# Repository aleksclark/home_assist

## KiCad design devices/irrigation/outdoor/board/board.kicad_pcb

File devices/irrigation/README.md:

# Irrigation Control

> **Status:** Planned

Two ESP32-based nodes for moisture sensing and automated irrigation.

## Nodes

### Indoor (`indoor/`)

- **Purpose:** Houseplant watering
- **Outputs:** 4 peristaltic pumps (one per plant/zone)
- **Sensors:** Capacitive soil moisture sensors
- **Board:** _TBD_

### Outdoor (`outdoor/`)

- **Purpose:** Garden drip irrigation
- **Outputs:** 4 solenoid valves controlling drip lines
- **Sensors:** Capacitive soil moisture sensors
- **Board:** _TBD_
- **Power:** Likely 24VAC solenoids with relay board

## Planned Features

- Per-zone moisture thresholds with hysteresis
- Manual override via Home Assistant
- Watering schedule fallback if HA is unreachable
- Moisture history logging

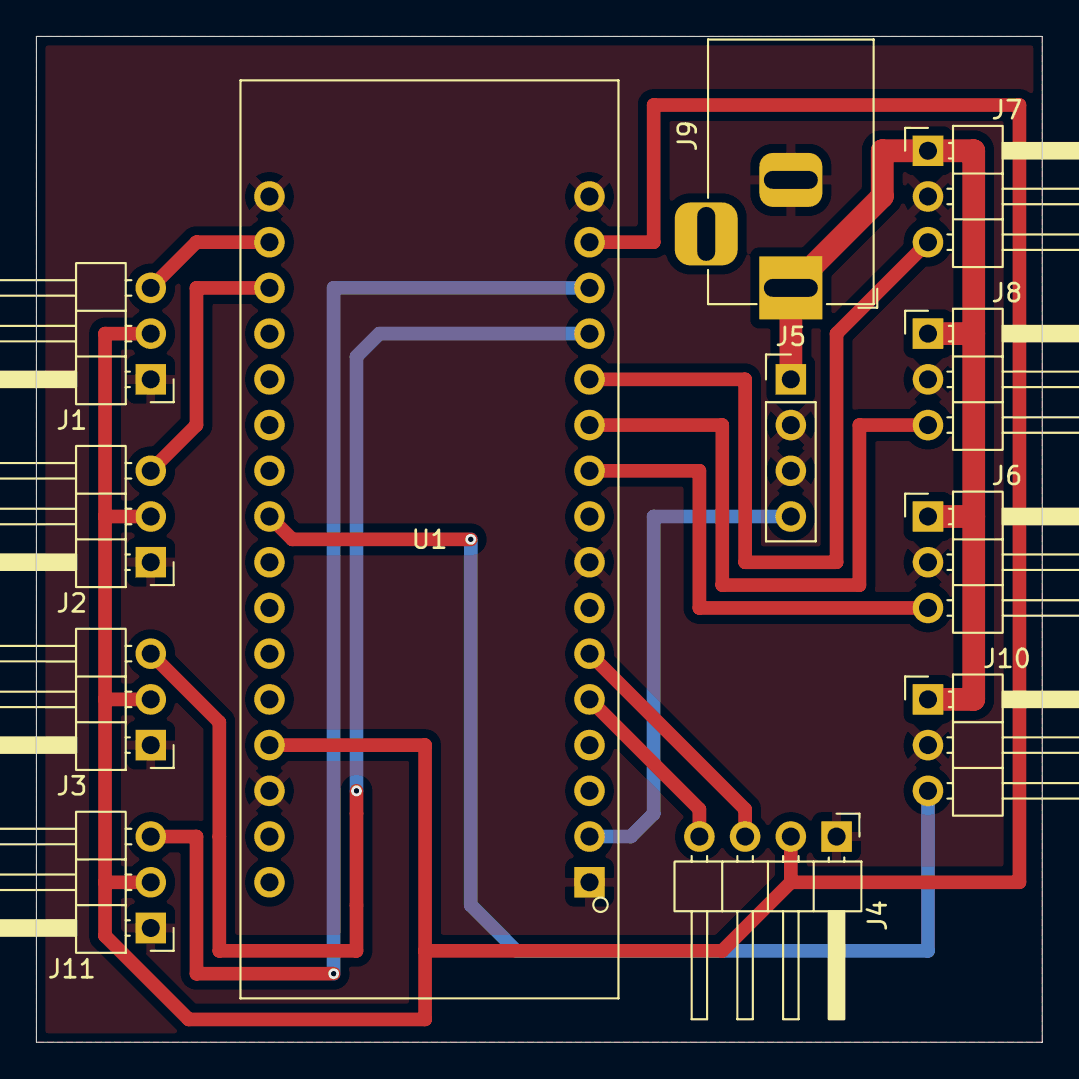
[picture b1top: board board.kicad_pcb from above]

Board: 2 copper layers, 55.9 x 55.9 mm, 12 parts (0 on the bottom side), 14 nets.

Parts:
J1, J2, J3, J11: Cap Sensor; PinHeader_1x03_P2.54mm_Horizontal
J4: GME12864; PinHeader_1x04_P2.54mm_Horizontal
J5: BUCK Conv; PinHeader_1x04_P2.54mm_Vertical
J6, J7, J8, J10: Relay Board; PinHeader_1x03_P2.54mm_Horizontal
J9: Barrel_Jack_MountingPin; BarrelJack_Horizontal
U1: CORE-ESP32-C3

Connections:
+3.3V: J1.2, J2.2, J3.2, J4.2, J11.2, U1.15 (+3V3), U1.20 (+3V3)
+5V: J5.4, U1.2 (VBUS)
+12V: J5.1, J6.1, J7.1, J8.1, J9.1, J10.1
GND: J1.1, J2.1, J3.1, J4.1, J5.2, J5.3, J6.2, J7.2, J8.2, J9.2, J10.2, J11.1, U1.1 (GND), U1.8 (GND), U1.16 (GND), U1.19 (GND), U1.32 (GND)
unnamed: J1.3, U1.31 (GPIO00/U1TXD)
unnamed: J2.3, U1.30 (GPIO01/U1RXD)
unnamed: J3.3, U1.13 (GPIO3)
unnamed: J4.3, U1.6 (GPIO5/ADC2/SCL)
unnamed: J4.4, U1.5 (GPIO4/ADC1/SDA)
unnamed: J6.3, U1.10 (GPIO7)
unnamed: J7.3, U1.12 (GPIO10)
unnamed: J8.3, U1.11 (GPIO6)
unnamed: J10.3, U1.25 (U0RXD)
unnamed: J11.3, U1.14 (GPIO2)

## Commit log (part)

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2026-03-07 Reorganize repo from flat bt_track/ into structured project layout
    Split the monolithic bt_track directory into devices/, esphome/, tools/,
    and home-assistant/ to cleanly separate device types and accommodate
    current and future projects (status display, irrigation nodes).
    🐘 Generated with Crush
    Assisted-by: AWS Claude Opus 4.6 via Crush <crush@charm.land>
2026-03-07 Add status display ESP32 firmware and ecobee research docs
    Status display: Rust firmware for ESP32-2432S028 (CYD) that registers
    with Home Assistant as a mobile_app device via webhook API and renders
    live sensor data (kitchen/bedroom temps, Della mini split, Ecobee) with
    incremental redraws. Code split into ha.rs (HA communication) and ui.rs
    (rendering/layout).
    Ecobee: research documents for ECB701 heat pump wiring diagnosis.
2026-03-10 Update Della mini split docs: rename to room-based entities, add kitchen AC
    - Recommend OpenBeken over ESPHome approach
    - Document WiFi AP configuration flow for OpenBeken modules
    - Rename existing entity from climate.della_mini_split to climate.livingroom_ac
    - Add second climate entity config for kitchen unit (climate.kitchen_ac)
    🐾 Generated with Crush
    Assisted-by: AWS Claude Opus 4.6 via Crush <crush@charm.land>
2026-03-12 Add outdoor irrigation controller and Della ESPHome config
    Outdoor irrigation: ESP32-C3 ESPHome firmware with 4-zone soil moisture
    sensing (ADC), 4 relay-controlled solenoid valves, SSD1306 OLED display,
    and Home Assistant integration. Includes wiring diagram and KiCad board.
    Della mini-splits: add custom TCL climate component for ESPHome migration,
    config YAML, setup docs, and Amos bedroom AC to HA MQTT config.
    🐮 Generated with Crush
2026-03-23 Fix HVAC automations, add display touch/dimming, persist HA config
    HVAC: fix boundary comparisons (<= / >=), switch Della automations to
    direct MQTT publish to bypass duplicate-entity conflicts, silence buzzer
    before each mode change, set daytime cool max to 73F.
    Status display: fix flicker with background-colored text rendering, add
    XPT2046 touch input and LEDC PWM backlight (dim after 3min, off after
    5min, tap to wake at 100%), fix display_status() to show actual HVAC
2026-04-13 fleet/blockyard: fix ansible deploy, add playbooks
    - Fix host_vars resolution: symlink host_vars/group_vars into
    inventory/ dir so Ansible finds them when inventory is specified
    as inventory/hosts.yml in ansible.cfg
    - systemd unit: add TimeoutStopSec=10, KillMode=mixed, SendSIGKILL
    to prevent systemctl stop from hanging when blockyard is stuck in
    Raft retry loops
2026-04-15 fix(hvac): reconcile automations, add deadband, remove Ecobee refs
    - Reconcile reference automations with live: use direct mqtt.publish
    with F-to-C conversion for Della units (was using climate.set_temperature
    which sends Fahrenheit through the entity layer)
    - Add 1.5°F deadband/hysteresis to all Della automations to prevent
    rapid cycling when temp oscillates around setpoint boundaries
    - Fix input_helpers.yaml daytime_cool_f initial: 75 -> 73 to match live
2026-04-15 Fix daytime cooling threshold to 74°F, align all HVAC config files
    Daytime cool setpoint was 73°F in deployed config and 75°F in reference
    config — standardized to 74°F across all files. Also corrected daytime
    heat_min comments/zones from 68→65 to match actual input_number values.
    🐘 Generated with Crush
    Assisted-by: AWS Claude Opus 4.6 via Crush <crush@charm.land>
2026-04-17 feat(hvac): add input_select.hvac_schedule_period to HA config
    New helper for the schedule dispatcher automation.
    Added include line to configuration.yaml.
2026-04-18 tcl_climate: add HEAT_COOL dual-setpoint mode
    When set to heat_cool, the ESP autonomously switches between heat and
    cool modes based on current temperature vs low/high setpoints. Reports
    HEAT_COOL to HA with two-point sliders while internally toggling the
    single-setpoint TCL protocol.
    In the deadband (between low and high), if the unit is already heating
    or cooling it keeps going. If idle, picks direction based on which side
2026-04-22 Update migration plan: NAS becomes node-4
    Major revision to account for NAS being wiped and reinstalled as
    node-4 in the fleet. Key changes:
    - 7-phase migration order designed for minimal disruption
    - Services migrate to fleet BEFORE NAS is touched
    - NAS converts last, bringing 4x5.5TB + 32GB RAM + QSV to the cluster
    - Jellyfin/PhotoPrism temporarily lose HW transcoding during soak,
2026-04-24 Update migration plan: reflect hardware additions
    - node-1: added 2x 1.8TB drives + 2.5G NIC (bond0)
    - node-2: added 1x 1.8TB drive + 2.5G NIC (bond0)
    - node-3: added 2.5G NIC (bond0)
    - All nodes now have balance-alb bonds (1G+2.5G)
    - Cluster now ~26TB raw (~10TB avail), up from ~18.5TB
    - Post node-4 conversion: ~48TB raw (was ~38TB)
2026-04-24 Migrate omada-controller from NAS to Nomad/node-3
    - Stopped on NAS, synced volumes to MooseFS /configs/omada/ (2CP)
    - Nomad job: host network, pinned to node-3 (L2 adjacency for APs)
    - 1.5GB memory (OOM at 1GB — Java+MongoDB needs headroom)
    - TCP health check with initial_status=passing (45s startup)
    - First service migrated from NAS to fleet
2026-04-24 Upgrade omada-controller 5.13 → 6.2
    - MongoDB upgraded 3.6 → 8.0 (stepped through 4.0/4.2/4.4/5.0/6.0/7.0/8.0)
    - Used mbentley/omada-controller:mongodb-upgrade-3.6-to-8 image
    - Pre-upgrade backup retained in data dir (mongodb-preupgrade.tar)
    - v6.2 deployment healthy on node-3
2026-04-24 Add Traefik reverse proxy as Nomad system job
    - Traefik v3.4 runs on all 3 fleet nodes (system job)
    - Listens on :80 (redirect to HTTPS), :443 (TLS), :8081 (dashboard/ping)
    - Nomad provider for auto-discovery of tagged services
    - Self-signed wildcard cert for *.fleet.local
    - insecureSkipVerify for backends with self-signed certs
    - Omada registered as first Traefik-routed service
2026-04-24 Add CoreDNS system job for fleet.lan DNS
    - CoreDNS runs on all 3 nodes as a Nomad system job
    - Serves fleet.lan zone with wildcard A records for Traefik
    - Individual node-{1,2,3}.fleet.lan records
    - Forwards non-fleet queries to 1.1.1.1/8.8.8.8
    - Changed from .local to .lan (mDNS conflict with systemd-resolved)
    - Updated omada traefik tags to fleet.lan
2026-04-24 Move fleet DNS to fleet.clark.team subdomain
    Wildcard under *.fleet.clark.team avoids conflicting with
    existing clark.team public DNS records.
2026-04-24 Deploy SigNoz monitoring stack to fleet
    - SigNoz (query service + UI) on port 8080
    - ClickHouse 25.5.6 for telemetry storage
    - ZooKeeper for ClickHouse coordination
    - OTel Collector receiving OTLP on 4317/4318
    - One-shot migrator with proper lifecycle ordering
    - All data on MooseFS (/mnt/moosefs/configs/signoz/)
2026-04-24 otel-agent: deploy fleet-wide telemetry collection
    - OTEL collector-contrib system job on all 3 nodes
    - Host metrics (CPU, memory, disk, network, load, processes)
    - Docker container stats via docker_stats receiver
    - Nomad Prometheus metrics scraping (enabled prometheus_metrics)
    - Docker container logs via filelog receiver
    - All data shipped to SigNoz otel-collector on node-2
2026-04-26 feat(media): add Traefik routing + .fleet.clark.team hostnames for all *arr services
    - All *arr services (sonarr, radarr, lidarr, prowlarr, bazarr, speakarr) and qbittorrent
    now have Traefik tags for HTTPS routing via X.fleet.clark.team
    - speakarr uses ghcr.io/hotio/radarr:release-6.1.1.10360 (readarr image)
    - qbittorrent: WebUI on port 8090, VPN_AUTO_PORT_FORWARD=false, WEBUI_PORTS env set
    - Download client configs updated to use qbittorrent.fleet.clark.team:443 (SSL)
    - Prowlarr applications updated to use HTTPS .fleet.clark.team URLs
2026-04-27 Add readarr Nomad job on port 8788 with Traefik routing
2026-04-27 Fix PhotoPrism: use existing family photo collection + DB
    - Mount originals from /mnt/moosefs/family/photos (existing collection)
    - Use existing storage at /mnt/moosefs/family/photoprism/storage
    - Use existing MariaDB database at /mnt/moosefs/family/photoprism/database
    - Set PHOTOPRISM_DISABLE_CHOWN=true (files already owned by uid 1000)
    - Reset DB passwords to match new deployment
2026-04-28 Add Jellyfin Nomad job — migrated from 192.168.0.3
    - Official jellyfin/jellyfin image on port 8096
    - Config on local disk at /home/aleks/jellyfin_config (node-2)
    - Media from MooseFS: /mnt/moosefs/media + /mnt/moosefs/family/photos
    - Traefik HTTPS routing via jellyfin.fleet.clark.team
    - 15m healthy deadline for image pulls
2026-04-28 Move Omada data to local SSD on node-3
    - MongoDB + WiredTiger is incompatible with MooseFS
    - Moved data to /home/aleks/omada_data on node-3 local disk
    - Removed unused host volume reference
    - Recovery in progress: mongorestore from pre-upgrade tar dump
2026-04-28 signoz: reduce ClickHouse resources (6GB->3GB RAM, 3000->2000 CPU)
    ClickHouse temp merge files flooded MooseFS trash with 58M entries,
    inflating mfsmaster metadata to 24GB. Root cause was unbounded memory
    and aggressive merging on a memory-constrained node.
    Nomad job changes:
    - ClickHouse memory: 6144 -> 3072 MB
    - ClickHouse CPU: 3000 -> 2000 MHz
2026-05-01 della: patched OpenBeken firmware with publish throttle and heat_cool mode
    Minisplits were dropping every 1-5 minutes due to watchdog resets caused by
    the TCL driver publishing 10 MQTT topics/sec unconditionally. Patched firmware
    (built from aleksclark/OpenBK7231T_App della-heat-cool branch) adds
    change-detection with 10s forced refresh, reducing steady-state publishes ~99%.
    Also adds dual-setpoint heat_cool mode, °F-to-°C guard for HA command topics,
    and fixes Buzzer/Display HA discovery payloads.
2026-05-04 cleanup: AGENTS.md, HA config snapshot, scripts, mosquitto job
    Updates AGENTS.md with full repo structure and fleet docs. Refreshes
    ha-config-snapshot, simplifies ha-download/upload scripts, adds
    configuration.yaml to tracked HA configs, and updates mosquitto Nomad job.
    🐮 Generated with Crush
    Assisted-by: AWS Claude Opus 4.6 via Crush <crush@charm.land>
2026-05-08 Remove manual mqtt.yaml climate entities — now auto-discovered via firmware
    The patched OpenBeken firmware publishes HA MQTT discovery messages for
    climate, buzzer switch, and display switch entities on boot. The manual
    mqtt.yaml definitions are no longer needed and would cause duplicate
    entities.
    Removed:
    - home-assistant/mqtt.yaml
2026-05-08 Shrink HVAC discovery JSON to fix heap exhaustion on RTL87x0C
    - Drop horizontal swing entirely (unused, saves ~200B heap + JSON)
    - Reduce fan modes to 3 levels: 1=quiet(mute), 2=medium(4), 3=powerful(turbo), auto
    - Reduce vertical swing to 2 options: none, move_full
    - Replace fanModeToStr lookup with switch mapping all HW speeds to 3 levels
    Combined savings: ~500+ bytes of cJSON tree + ~300 bytes serialized JSON,
    bringing the climate discovery payload well under the RTL87x0C heap limit.
2026-06-26 Add node-5 to fleet inventory (Dell Precision 5810, compute-only)
    - 192.168.0.9, Xeon E5-1603 v4 (4 cores), 16GB RAM
    - 112GB ADATA SSD (btrfs), no data disks
    - GTX 960 present but no driver (headless fleet node)
    - Cleaned V100 SXM2 artifacts (PCI rescan service, nvidia-v100.conf, GRUB pci=realloc)
    - Removed cuda, nvidia-open-lts, nvidia-utils, nvidia-container-toolkit
    - Compute-only role, Nomad node class: compute
2026-06-26 Add GPU metrics pipeline + fix node-6 Nomad bind interface
    - Added GPU prometheus scrape job to otel-agent (port 9835)
    - Deployed gpu_exporter.py systemd service on node-6 (nvidia-smi -> prometheus)
    - Fixed node-6 nomad_bind_interface: bond0 (was eno1, a bond slave with no IP)
    - GPU metrics now flowing to SigNoz: utilization, memory, temp, power
    - Added GPU Utilization + GPU Memory panels to Clark Fleet Command dashboard
2026-06-26 signoz: bump zookeeper memory 768->1024MB (430 OOM restarts)
2026-06-26 Add goshelf Nomad job
